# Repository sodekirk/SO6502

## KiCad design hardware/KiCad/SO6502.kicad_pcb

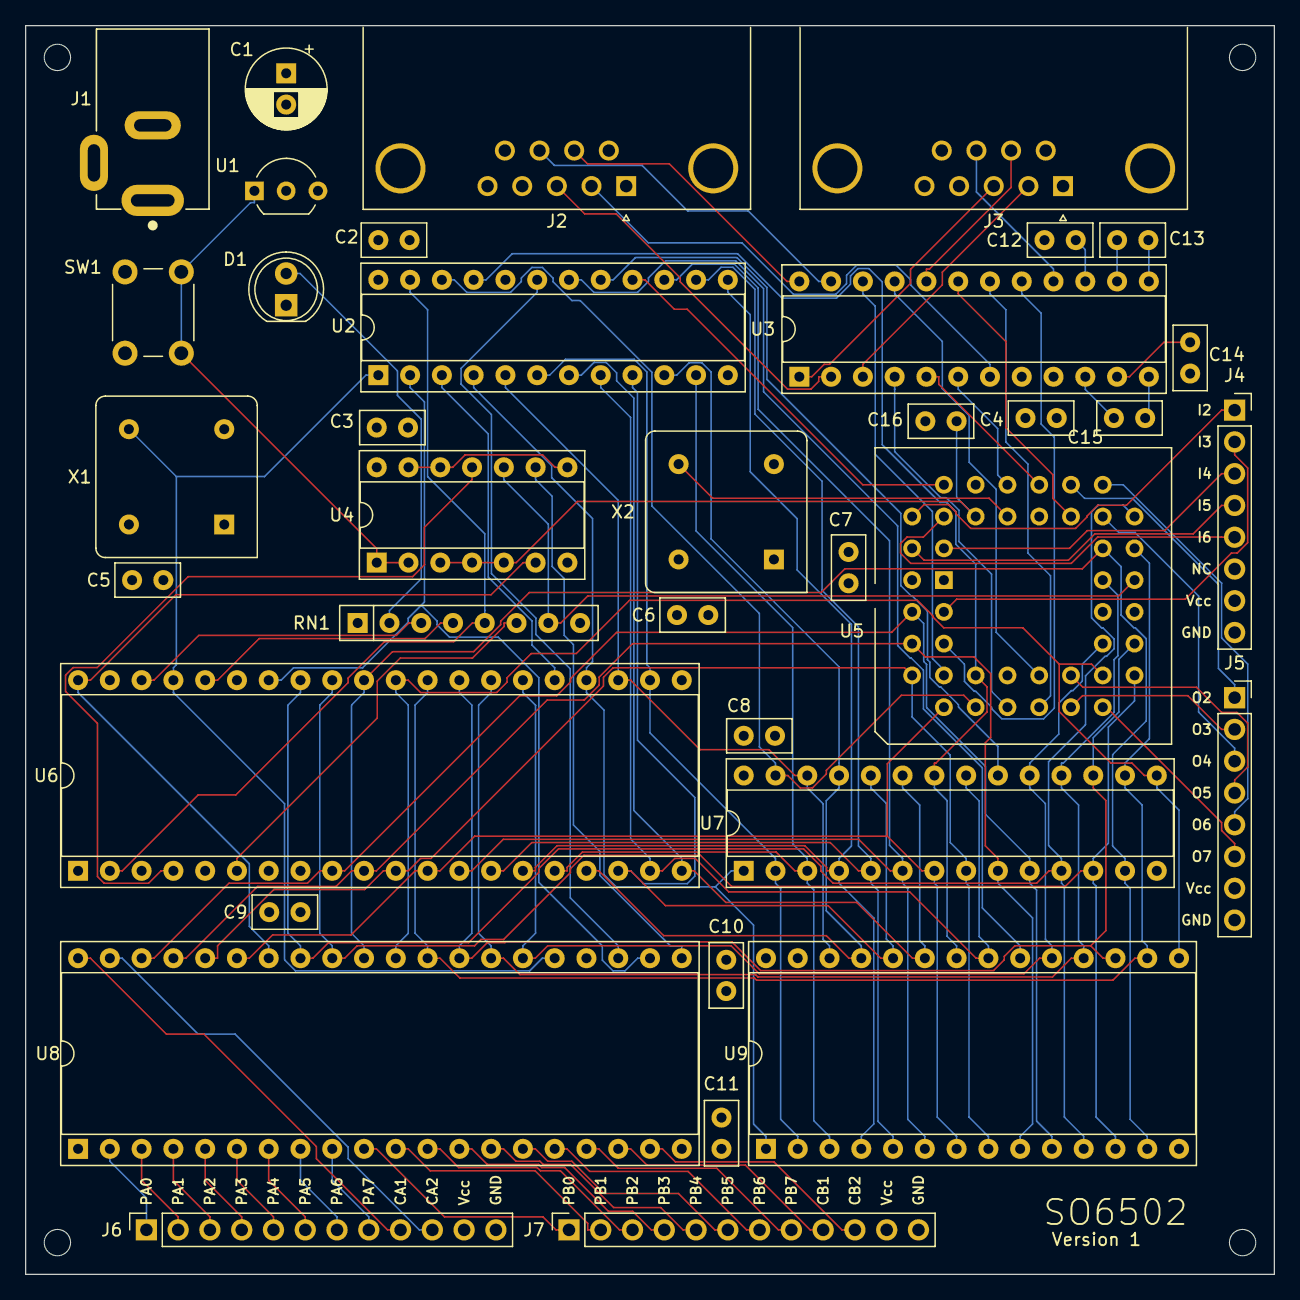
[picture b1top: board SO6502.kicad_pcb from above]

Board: 4 copper layers, 99.8 x 99.8 mm, 41 parts (0 on the bottom side), 100 nets.

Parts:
C1: 100uF; CP_Radial_D6.3mm_P2.50mm
C2, C3, C4, C5, C6, C7, C8, C9, C10, C11, C16: 0.1uF; C_Disc_D5.0mm_W2.5mm_P2.50mm
C12, C13, C14, C15: 1uF; C_Disc_D5.0mm_W2.5mm_P2.50mm
D1: LED; LED_D5.0mm
H1, H2, H3, H4: MountingHole; MountingHole_2.1mm
J1: PJ-002A; CUI_PJ-002A
J2, J3: DB9_Male; DSUB-9_Male_Horizontal_P2.77x2.84mm_EdgePinOffset9.90mm_Hou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
J4, J5: Conn_01x08_Female; PinSocket_1x08_P2.54mm_Vertical
J6, J7: Conn_01x12_Female; PinSocket_1x12_P2.54mm_Vertical
RN1: R_Network07_US; R_Array_SIP8
SW1: SW_Push; SW_PUSH_6mm
U1: DS1813; TO-92_Inline_Wide
U2: ATF22V10; DIP-24_W7.62mm_Socket
U3: MAX238; DIP-24_W7.62mm_Socket
U4: 74HC00; DIP-14_W7.62mm_Socket
U5: SC28L92; PLCC-44_THT-Socket
U6: W65C02; DIP-40_W15.24mm_Socket
U7: 71256SA; DIP-28_W7.62mm_Socket
U8: W65C22; DIP-40_W15.24mm_Socket
U9: 28C256; DIP-28_W15.24mm_Socket
X1, X2: CXO_DIP8; Oscillator_DIP-8

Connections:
A0: U5.2, U6.9, U7.10, U8.38, U9.10
A1: U5.4, U6.10, U7.9, U8.37, U9.9
A2: U5.6, U6.11, U7.8, U8.36, U9.8
A3: U5.7, U6.12, U7.7, U8.35, U9.7
A4: U2.15, U6.13, U7.6, U9.6
A5: U2.14, U6.14, U7.5, U9.5
A6: U2.13, U6.15, U7.4, U9.4
A7: U2.11, U6.16, U7.3, U9.3
A8: U2.10, U6.17, U7.25, U9.25
A9: U2.9, U6.18, U7.24, U9.24
A10: U2.8, U6.19, U7.21, U9.21
A11: U2.7, U6.20, U7.23, U9.23
A12: U2.6, U6.22, U7.2, U9.2
A13: U2.5, U6.23, U7.26, U9.26
A14: U2.4, U6.24, U7.1, U9.1
A15: U2.3, U6.25
BE: RN1.4, U6.36
CA1: J6.9, U8.40
CA2: J6.10, U8.39
CB1: J7.9, U8.18
CB2: J7.10, U8.19
CS2892: U2.16, U5.39
CS6522: U2.19, U8.23
CSRAM: U2.17, U7.20
CSROM: U2.18, U9.20
CTSa: J2.8, U3.23
CTSb: J3.8, U3.16
D0: U5.28, U6.33, U7.11, U8.33, U9.11
D1: U5.18, U6.32, U7.12, U8.32, U9.12
D2: U5.27, U6.31, U7.13, U8.31, U9.13
D3: U5.19, U6.30, U7.15, U8.30, U9.15
D4: U5.26, U6.29, U7.16, U8.29, U9.16
D5: U5.20, U6.28, U7.17, U8.28, U9.17
D6: U5.25, U6.27, U7.18, U8.27, U9.18
D7: U5.21, U6.26, U7.19, U8.26, U9.19
DCTSa: U3.22, U5.8
DCTSb: U3.17, U5.5
DRTSa: U3.19, U5.32
DRTSb: U3.21, U5.14
DRxDa: U3.6, U5.35
DRxDb: U3.4, U5.11
DTxDa: U3.5, U5.33
DTxDb: U3.18, U5.13
GND: C1.2, C2.2, C3.2, C4.2, C5.2, C6.2, C7.2, C8.2, C9.2, C10.2, C11.2, C12.2, C16.2, D1.1, J1.2, J1.3, J2.5, J3.5, J4.8, J5.8, J6.12, J7.12, SW1.2, U1.3, U2.12, U3.8, U4.7, U5.22, U6.21, U7.14, U8.1, U9.14, X1.4, X2.4
IP2: J4.1, U5.40
IP3: J4.2, U5.3
IP4: J4.3, U5.43
IP5: J4.4, U5.42
IP6: J4.5, U5.41
IRQ1B: U4.9, U8.21
IRQ2B: RN1.7, U4.10, U5.24
IRQB: U4.11, U6.4
NMIB: RN1.6, U6.6
unnamed: C12.1, U3.15
unnamed: C13.1, U3.14
unnamed: C13.2, U3.13
unnamed: C14.2, U3.11
unnamed: C15.1, U3.10
unnamed: C15.2, U3.12
unnamed: D1.2, RN1.2
unnamed: SW1.1, U1.1, U4.1, U4.2
unnamed: U4.8, U4.12, U4.13
OP2: J5.1, U5.31
OP3: J5.2, U5.15
OP4: J5.3, U5.30
OP5: J5.4, U5.16
OP6: J5.5, U5.29
OP7: J5.6, U5.17
PA0: J6.1, U8.2
PA1: J6.2, U8.3
PA2: J6.3, U8.4
PA3: J6.4, U8.5
PA4: J6.5, U8.6
PA5: J6.6, U8.7
PA6: J6.7, U8.8
PA7: J6.8, U8.9
PB0: J7.1, U8.10
PB1: J7.2, U8.11
PB2: J7.3, U8.12
PB3: J7.4, U8.13
PB4: J7.5, U8.14
PB5: J7.6, U8.15
PB6: J7.7, U8.16
PB7: J7.8, U8.17
PHI2: U2.1, U6.37, U8.25, X1.5
RD: U2.21, U5.10, U7.22, U9.22
RDY: RN1.5, U2.23, U6.2
RESB: U4.6, U6.40, U8.34
RESET: C16.1, U4.3, U4.4, U4.5, U5.38
RTSa: J2.7, U3.24
RTSb: J3.7, U3.20
RWB: U2.2, U6.34, U8.22
RxDa: J2.2, U3.7
RxDb: J3.2, U3.3
SOB: RN1.3, U6.38
TxDa: J2.3, U3.2
TxDb: J3.3, U3.1
Vcc: C1.1, C2.1, C3.1, C4.1, C5.1, C6.1, C7.1, C8.1, C9.1, C10.1, C11.1, C14.1, J1.1, J4.7, J5.7, J6.11, J7.11, RN1.1, U1.2, U2.24, U3.9, U4.14, U5.12, U5.44, U6.8, U7.28, U8.20, U8.24, U9.27, U9.28, X1.8, X2.8
WR: U2.22, U5.9, U7.27
X1: U5.36, X2.5

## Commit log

2025-12-27 Fix spelling error
2025-12-27 Add/update README.md files
2025-12-27 Update README.md files
